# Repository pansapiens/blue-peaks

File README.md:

# Blue Peaks

A low-cost remix of [Mutable instrument's Peaks](https://mutable-instruments.net/modules/peaks/) and [Matias Levy Alfie's $peaks](https://github.com/matias-levy/peaks).

## Description
This is a 'skiff friendly' remix of Matias Levy Alfie's awesome [$peaks](https://github.com/matias-levy/peaks) module (which in turn is based on [Mutable instrument's Peaks](https://mutable-instruments.net/modules/peaks/)), with the PCB redesigned with a depth of 50 cm. See [Matias repo](https://github.com/matias-levy/peaks) for details on how he redesigned the module to use a Blue Pill without an external DAC !

It also includes versions of the original Peaks and the Dead Man's Catch firmwares trimmed to fit on a Blue Pill (STM32F103C8T6 dev board) with only 64k of flash. You can use this firmware with Matias' $peaks if you prefer to make that PCB.

Like Matias' original remix, the project is designed to use a single sided home-etched PCB with ~~a couple of~~ far too many jumper wires.
## Firmwares
There's the option to flash one of two firmwares that where ported. The original Mutable Instruments one is in the `firmware/peaks` directory. The [Mutated Mutables Dead Man's Catch](https://github.com/timchurches/Mutated-Mutables/tree/master/peaks) is in the `firmware/peaks2`.

By default the "Number Station" Easter egg in the firmware is disabled to allow it to fit on a Blue Pill with 64k of flash. If you have 128k of flash it can be enabled in the `makefile` (see below).

Compiled binaries and HEX files are provided for both under `firmware/build`.

## Matias changes from Peaks
* Added a driver for the PWM DAC running at **14 bit depth, 48Khz sampling rate.** (File in firmware/peaks/drivers/pwm_dac.h)
* Activated the clock for the TIM4 in firmware/peaks/drivers/system.cc
* **Bypassed the bootloader:** This was done as to simplify the code, it does not interfere with the calibration functionality of the module.
* Redesigned the output portion of the hardware to accommodate to the PWM levels.

## Further changes from $peaks
* Modified board layout to be 'skiff friendly' (PCB is 50mm deep, 110 mm high)
* Disabled the "Number Station" Easter egg by default, to fit in 64k flash.
* Tweaked to use default KiCad footprints, less vertically mounted resistors, use 9mm horizontal Alpha-style pots (eg RD901F / RK09)
* Use 5.1V Zener diodes rather than 3.6V.
* Tweaked tracks to work better for my own PCB production method (pen plotter + etching)

## Build guide

Mine looked like this. You are on your own ... have fun !

Yup, it's a rat's nest. I would love to find the time to redesign further to limit the number of jumper wires.

**WARNING WARNING WARNING** - I found some weirdness in the orientation / side of PCB that some components needed to be soldered in this design. By the time I discovered it I'd already made the PCBs so I worked around it. I ended up soldering the Blue Pill on the opposite side to the other components (awkward), and flipping the transistors, voltage regulator, TL074 and power socket 180 degrees to ensure the pinouts correctly aligned with the approriate tracks / schematic. So fair warning - be paranoid about component orientation and don't blindly trust the silkscreen layer. Visually check that the pins you are soldering make sense with the tracks they connect to (eg wide ground trace). If you don't check carefully as you go, you'd better enjoy desoldering components ....

## Flashing and development
Build with:
```
cd firmware
make -f peaks/makefile
make -f peaks/makefile bin
```

You'll need Python 2.x and `numpy`, as well as a typical Linux build environment for ARM cross-compilation 
(eg On Ubuntu 20.04, do `sudo apt install gcc-arm* build-essential` and set `TOOLCHAIN_PATH = /usr/` in `firmware/peaks/makefile`).

If you happen to have a Blue Pill with 128k of flash, you can enable the "Number Station" Easter egg by uncommenting the `NUMBER_STATION` variable in `firmware/peaks/makefile`.

To make it easier there are pre-compiled binaries and .HEX files in `firmware/build`, this can be flashed directly to the bluepill using [STM32CubeProgrammer](https://www.st.com/en/development-tools/stm32cubeprog.html).

Another option is to install the [mutable-dev-environment](https://github.com/pichenettes/mutable-dev-environment) and replace the peaks folder with the one inside /firmware, then executing

    make -f peaks/makefile upload_serial

We use this command because the bootloader is bypassed.

## Thanks
Many thanks Emilie Gillet for open-sourcing her work which is a constant inspiration for many musicians and makers, and encourage everyone interested in this project to checkout the [Mutable instrument's Forum](https://forum.mutable-instruments.net/) in which Emilie is a very active member.

## TODO, IDEAS

- Resolve issues with flipped components / which side to solder / front vs. back traces.
  - To get correct connections I needed to solder the Blue Pill pin header sockets on the 'wrong' side of the PCB 
    (the opposite side to other components - quite awkward on a single sided PCB),
    and rotate the TL074, transistors and voltage regulator 180 degrees to allow them to be correctly soldered to 
    the 'right' side of the board.
    
- Change some GPIOs in the firmware to make PCB layout easier/cleaner.
- Use a 3.3V supply to power the Blue Pill (eg via LD1117AV33 / LM1117-3.3) rather than 5V - apparently the 5V to 3.3V regulator on Blue Pill boards can't handle more the 100mA, so it's safer to supply 3.3V directly.
- For matching R14/R16 to the Zener reference voltage, 21k and 14k resistors are tricky to find. Either use a 20+1k / 13+1k (or maybe use a resistor + 1k or 2k trimpot to allow manual calibration ?)
- Create a two PCB design with pots/jacks/switches soldered on front board. The single board version is a mess of wires.
- Add CV control for each of the four pots !

While I don't plan to tackle any of these changes within the foreable future, I figured it was worth documenting.

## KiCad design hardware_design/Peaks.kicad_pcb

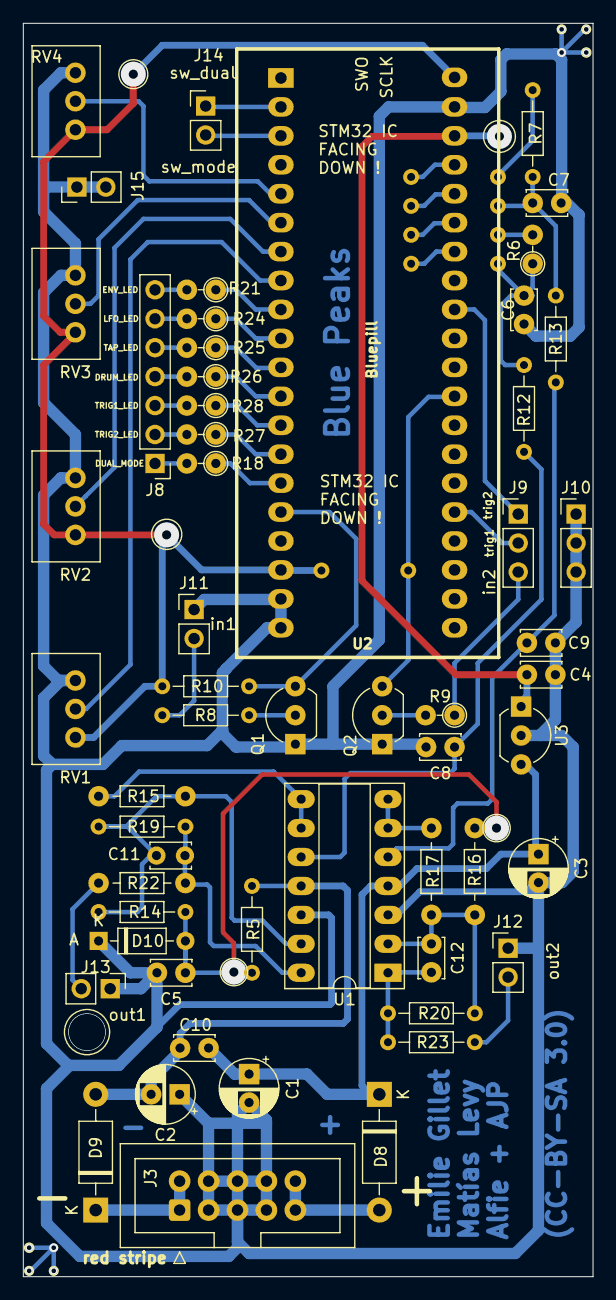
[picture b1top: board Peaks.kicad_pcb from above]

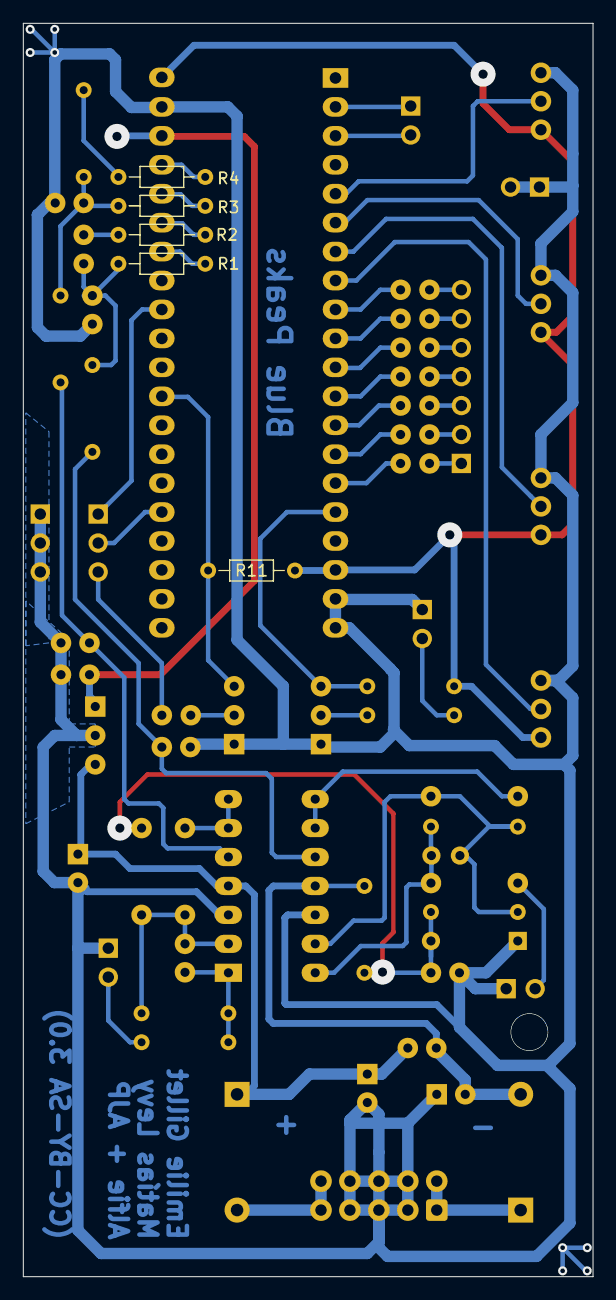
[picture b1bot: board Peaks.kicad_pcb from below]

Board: 2 copper layers, 50.0 x 110.0 mm, 61 parts (5 on the bottom side), 54 nets.

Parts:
C1, C2: 10u; CP_Radial_D5.0mm_P2.50mm_Large_Pads
C3: 0,33u; CP_Radial_D5.0mm_P2.50mm_Large_Pads
C4, C5, C10: 100n; C_Disc_D3.4mm_W2.1mm_P2.50mm_Large_Pads
C6, C7, C8, C9: 4.7n; C_Disc_D3.4mm_W2.1mm_P2.50mm_Large_Pads
C11: 150pf; C_Disc_D3.4mm_W2.1mm_P2.50mm
C12: 150pf; C_Disc_D3.4mm_W2.1mm_P2.50mm_Large_Pads
D8, D9: 1N5817; D_DO-41_SOD81_P10.16mm_Horizontal
D10: 5.1; D_DO-35_SOD27_P7.62mm_Horizontal
J3: Eurorack Power; IDC-Header_2x05_P2.54mm_Vertical_Large_Pads
J8: Conn_01x07; PinHeader_1x07_P2.54mm_Vertical
J9, J10: PinHeader_1x03_P2.54mm_Vertical
J11, J12, J13, J14, J15: PinHeader_1x02_P2.54mm_Vertical
Q1, Q2: 2N3904; TO-92_Inline_Wide_Large_Pads
R1, R3, R12, R13: 1k5; R_Axial_DIN0204_L3.6mm_D1.6mm_P7.62mm_Horizontal
R2, R4: 180k; R_Axial_DIN0204_L3.6mm_D1.6mm_P7.62mm_Horizontal
R5, R10, R11: 10k; R_Axial_DIN0204_L3.6mm_D1.6mm_P7.62mm_Horizontal
R6: 12k; R_Axial_DIN0204_L3.6mm_D1.6mm_P2.54mm_Vertical_Large_Pads
R7: 12k; R_Axial_DIN0204_L3.6mm_D1.6mm_P7.62mm_Horizontal
R8: 100k; R_Axial_DIN0204_L3.6mm_D1.6mm_P7.62mm_Horizontal
R9: 100k; R_Axial_DIN0204_L3.6mm_D1.6mm_P2.54mm_Vertical_Large_Pads
R14: 21k; R_Axial_DIN0204_L3.6mm_D1.6mm_P7.62mm_Horizontal
R15, R17: 6k8; R_Axial_DIN0204_L3.6mm_D1.6mm_P7.62mm_Horizontal_Large_Pads
R16: 21k; R_Axial_DIN0204_L3.6mm_D1.6mm_P7.62mm_Horizontal_Large_Pads
R18, R21, R24, R25, R26, R27, R28: 2k; R_Axial_DIN0204_L3.6mm_D1.6mm_P2.54mm_Vertical_Large_Pads
R19, R20: 33k; R_Axial_DIN0204_L3.6mm_D1.6mm_P7.62mm_Horizontal
R22: 1k; R_Axial_DIN0204_L3.6mm_D1.6mm_P7.62mm_Horizontal_Large_Pads
R23: 1k; R_Axial_DIN0204_L3.6mm_D1.6mm_P7.62mm_Horizontal
RV1, RV2, RV3, RV4: B10k; Potentiometer_Alps_RK097_Single_Horizontal
U1: TL074; DIP-14_W7.62mm_Socket_LongPads
U2: Bluepill; BluePill_STM32F103C
U3: 78l05; TO-92_Inline_Wide_Large_Pads

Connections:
3.3V: R10.1, R11.1, RV1.3, RV2.3, RV3.3, RV4.3, U2.18, U2.40
+5V: C4.1, U2.38, U3.1
+12V: C1.1, C3.1, C10.1, D8.1, U1.4, U3.3
-12V: C2.2, C10.2, D9.2, R5.2, U1.11
/CH1_PWM1: R1.2, U2.34
/CH1_PWM2: R2.2, U2.35
/CH2_PWM1: R3.2, U2.36
/CH2_PWM2: R4.2, U2.37
/LED1: R18.1, U2.15
/LED2: R21.1, U2.9
/LED3: R24.1, U2.10
/LED4: R25.1, U2.11
/LED5: R26.1, U2.12
/LED_SALIDA_1: R27.1, U2.14
/LED_SALIDA_2: R28.1, U2.13
/POT_1: RV1.2, U2.8
/POT_2: RV2.2, U2.7
/POT_3: RV3.2, U2.6
/POT_4: RV4.2, U2.5
/REF_-3.6: C5.1, D10.2, R5.1, R14.2, R16.2
/SW_DUAL: J14.1, U2.2
/SW_MODE: J14.2, U2.3
/SW_TRIG1: J9.2, U2.25
/SW_TRIG2: J9.1, U2.32
/TRIG_1: Q1.3, R10.2, U2.16
/TRIG_2: Q2.3, R11.2, U2.29
GND: C1.2, C2.1, C3.2, C4.2, C5.2, C6.2, C7.2, C8.2, C9.2, D10.1, J3.3, J3.4, J3.5, J3.6, J3.7, J3.8, J10.1, J10.2, J10.3, J11.1, J12.1, J13.1, J15.1, J15.2, Q1.1, Q2.1, RV1.1, RV2.1, RV3.1, RV4.1, U1.3, U1.12, U2.19, U2.20, U2.39, U3.2
unnamed: C6.1, R1.1, R6.1, R12.2
unnamed: C7.1, R3.1, R7.1, R13.2
unnamed: C8.1, R12.1, U1.10
unnamed: C9.1, R13.1, U1.5
unnamed: C11.1, R14.1, R15.1, R19.2, U1.13
unnamed: C11.2, R19.1, R22.2, U1.14
unnamed: C12.1, R16.1, R17.1, R20.2, U1.2
unnamed: C12.2, R20.1, R23.2, U1.1
unnamed: D8.2, J3.9, J3.10
unnamed: D9.1, J3.1, J3.2
unnamed: Q1.2, R8.2
unnamed: Q2.2, R9.2
unnamed: R2.1, R6.2
unnamed: R4.1, R7.2
unnamed: R15.2, U1.8, U1.9
unnamed: R17.2, U1.6, U1.7
TO_D1: J8.1, R18.2
TO_D2: J8.7, R21.2
TO_D3: J8.6, R24.2
TO_D4: J8.5, R25.2
TO_D5: J8.4, R26.2
TO_D6: J8.2, R27.2
TO_D7: J8.3, R28.2
TO_IN1: J11.2, R8.1
TO_IN2: J9.3, R9.1
TO_OUT1: J13.2, R22.1
TO_OUT2: J12.2, R23.1

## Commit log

2021-04-11 More portable Python shebang.
    Remove unnesscary pyc files.
    Add .gitignore.
2021-04-12 Make Number Station optional for 64k flash boards.
    New builds for 64k Blue Pills.
    README notes about changes.
2021-04-13 Make Number Station optional for 'peaks2' firmware.
    Moved bytebeats into it's own directory.
    Dead Man's Catch will fit on a 64k flash Blue Pill if Number Station isn't included.
2021-04-16 Update name in source files
2021-04-16 Remixed hardware.
    Skiff friendly (50cm depth) PCB.
    Revert to using more standard KiCad footprints.
    Use a 5.1V Zener diode for PWM scaling.
2021-04-16 Add 3D printable front panel design.
2021-04-16 Remove original front panel design.
    The old front panel template probably doesn't fit the new PCB design here, so I've removed it.
2021-04-21 Update README for this remix, new photos.
2021-04-26 Add compile option to reverse the direction of the pots (on by default).
    Bugfix to NUMBER_STATION conditional compile.
2021-05-02 Compilation option to reverse pot order.
    Seems the current design has the pots wired in reverse order (or I just did it wrong). The REVERSE_POT_ORDER option in the makefile allows this to be corrected in the firmware).

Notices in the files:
hardware_design/Peaks.kicad_pcb:
(CC-BY-SA 3.0)
